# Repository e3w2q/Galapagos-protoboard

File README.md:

# Galapagos Protoboard

## Important point

All functions have not yet been verified on an actual device.

The microcontroller is one of the following: Pro Micro, Raspberry Pi Pico, or Xiao RP2040.

The key matrix is using duplex matrix.

You can use a rotary encoder or a joystick.

The joystick is one of the following:  ALPS RKJXV122400R, Nintendo Switch Joystick for Joy-Cons,  or Sparkfan joystick.

You may be able to use a trackball.

## Pin assign

### Key switch

|                         | Pro Micro | Raspberry Pi Pico | Xiao RP2040 |
| ----------------------- | --------- | ----------------- | ----------- |
| Upper left key switch   | F5 to D4  | GP9 to GP2        | GP6 to GP26 |
| Lower left key switch   | F5 to C6  | GP9 to GP3        | GP6 to GP27 |
| Upper middle key switch | D4 to F6  | GP2 to GP10       | GP26 to GP7 |
| Lower middle key switch | C6 to F6  | GP3 to GP10       | GP27 to GP7 |
| Upper right key switch  | D4 to F5  | GP2 to GP9        | GP26 to GP6 |
| Lower right key switch  | C6 to F5  | GP3 to GP9        | GP27 to GP6 |

### Rotary Encoder

|             | Pro Micro | Raspberry Pi Pico | Xiao RP2040 |
| ----------- | --------- | ----------------- | ----------- |
| A           | D1        | GP20              | No assign   |
| B           | D0        | GP21              | No assign   |
| Push switch | B6        | GP22              | No assign   |

### Joystick

|             | Pro Micro | Raspberry Pi Pico | Xiao RP2040 |
| ----------- | --------- | ----------------- | ----------- |
| Horizontal  | D1        | GP20              | No assign   |
| Vertical    | D0        | GP21              | No assign   |
| Push switch | B6        | GP22              | No assign   |

### Trackball

|             | Pro Micro | Raspberry Pi Pico | Xiao RP2040 |
| ----------- | --------- | ----------------- | ----------- |
| MISO        | B3        | GP16              | No assign   |
| MOSI        | B2        | GP19              | No assign   |
| SCLK        | B1        | GP18              | No assign   |
| NCS         | F7        | GP17              | No assign   |

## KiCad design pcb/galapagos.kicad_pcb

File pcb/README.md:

# Galapagos Protoboard

## Schematic
[Schematic PDF](../image/ukiha.pdf?raw=true)

## PCB Layout

## Acrylic Layout

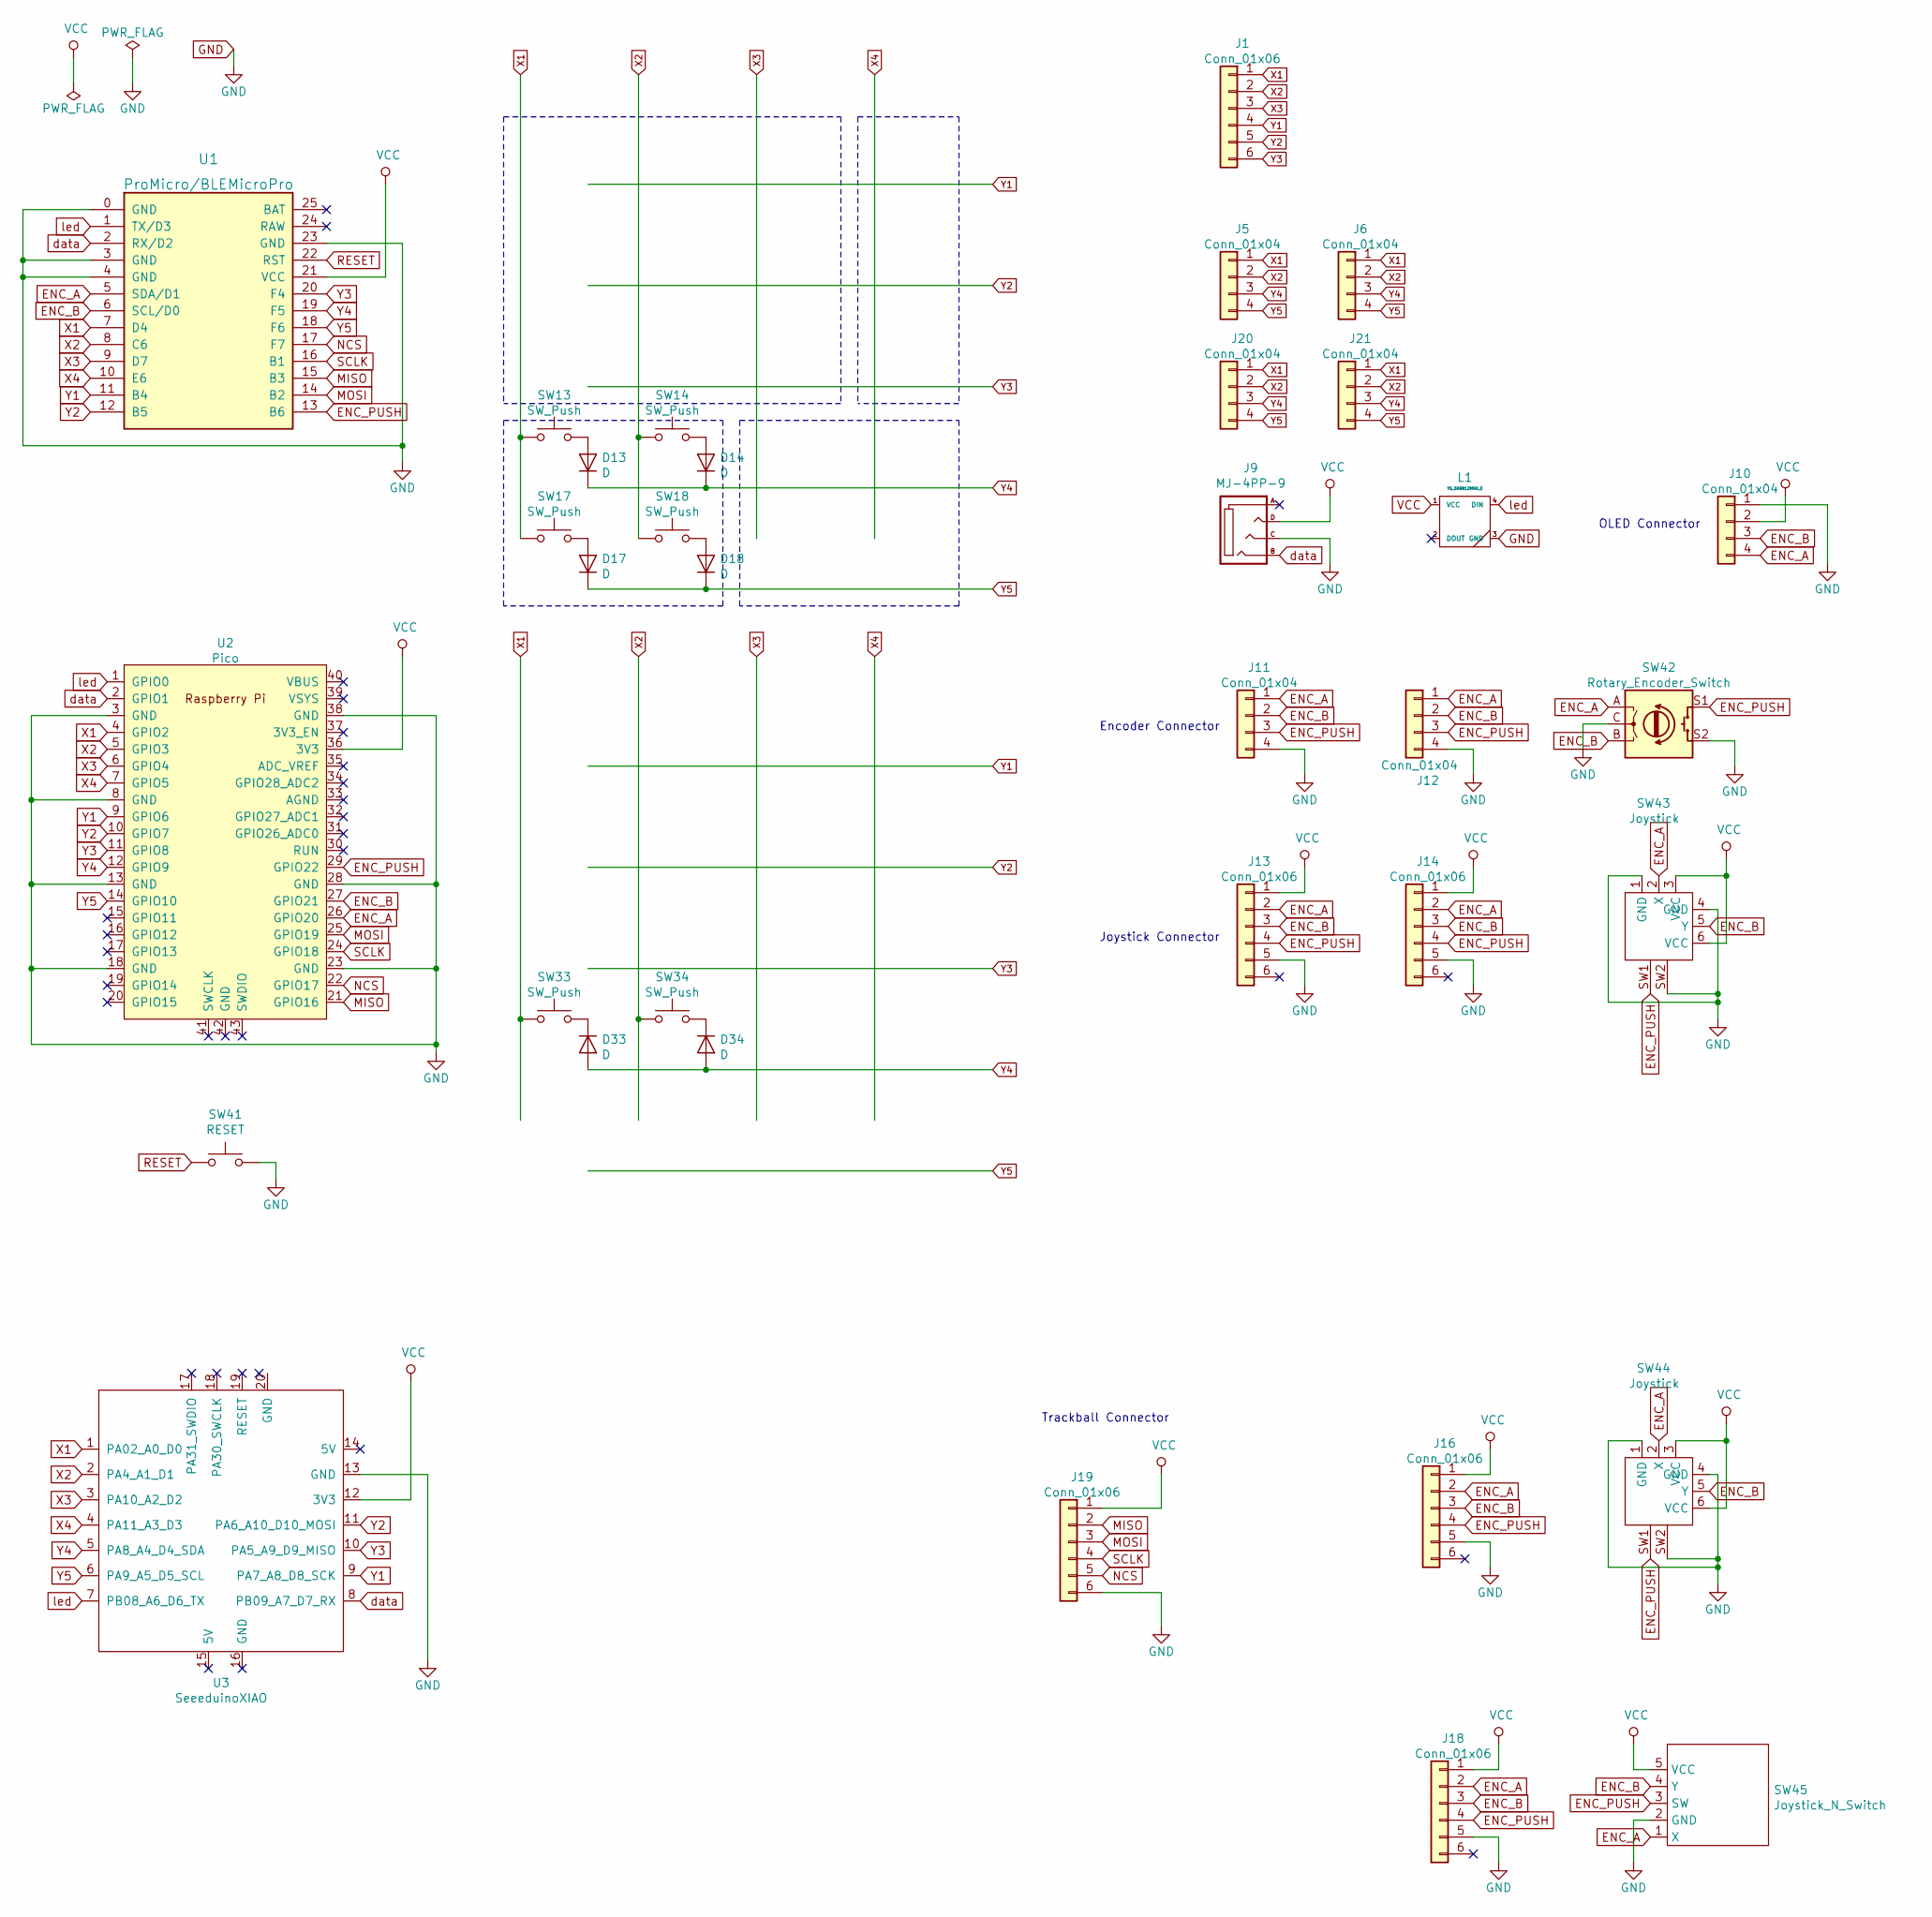
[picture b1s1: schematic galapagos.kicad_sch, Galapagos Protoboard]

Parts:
D13, D14, D17, D18, D33, D34: D; diode_TH_SMD_rev3
J1, J13, J14, J16, J18, J19: Conn_01x06; JST_SH_BM03B-SRSS-TB_1x06-1MP_P1.00mm_Vertical
J5, J6, J11, J12: Conn_01x04; JST_SH_BM03B-SRSS-TB_1x04-1MP_P1.00mm_Vertical
J9: MJ-4PP-9; MJ-4PP-9_reversible
J10: Conn_01x04; PinHeader_1x04_P2.54mm_Vertical
J20, J21: Conn_01x04; JST_ZH_1x04_P1.50mm_Vertical
L1: YS_SK6812MINI_E; YS-SK6812MINI-E
SW13, SW14, SW17, SW18, SW33, SW34: SW_Push; CherryMX_MidHeight_Choc_Hotswap_rev8_test
SW41: RESET; ResetSW
SW42: Rotary_Encoder_Switch; RotaryEncoder_Alps_EC11E-Switch_Vertical_H20mm_rev2
SW43: Joystick; Joystick_AE-RKJXV122400R
SW44: Joystick; Joystick_Sparkfan
SW45: Joystick_N_Switch
U1: ProMicro/BLEMicroPro; ArduinoProMicro_ConThrough
U2: Pico; RPi_Pico_SMD_TH_rev3
U3: SeeeduinoXIAO; Seeeduino XIAO RP2040

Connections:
ENC_A: J10.4, J11.1, J12.1, J13.2, J14.2, J16.2, J18.2, SW42.A, SW43.2 (X), SW44.2 (X), SW45.1 (X), U1.5 (SDA/D1), U2.26 (GPIO20)
ENC_B: J10.3, J11.2, J12.2, J13.3, J14.3, J16.3, J18.3, SW42.B, SW43.5 (Y), SW44.5 (Y), SW45.4 (Y), U1.6 (SCL/D0), U2.27 (GPIO21)
ENC_PUSH: J11.3, J12.3, J13.4, J14.4, J16.4, J18.4, SW42.S1, SW43.SW1, SW44.SW1, SW45.3 (SW), U1.13 (B6), U2.29 (GPIO22)
GND: J9.C, J10.1, J11.4, J12.4, J13.5, J14.5, J16.5, J18.5, J19.6, L1.3 (GND), SW41.2, SW42.C, SW42.S2, SW43.1 (GND), SW43.4 (GND), SW43.SW2, SW44.1 (GND), SW44.4 (GND), SW44.SW2, SW45.2 (GND), U1.0 (GND), U1.3 (GND), U1.4 (GND), U1.23 (GND), U2.3 (GND), U2.8 (GND), U2.13 (GND), U2.18 (GND), U2.23 (GND), U2.28 (GND), U2.38 (GND), U3.13 (GND)
MISO: J19.2, U1.15 (B3), U2.21 (GPIO16)
MOSI: J19.3, U1.14 (B2), U2.25 (GPIO19)
NCS: J19.5, U1.17 (F7), U2.22 (GPIO17)
unnamed: D13.2 (A), SW13.2
unnamed: D14.2 (A), SW14.2
unnamed: D17.2 (A), SW17.2
unnamed: D18.2 (A), SW18.2
unnamed: D33.1 (K), SW33.2
unnamed: D34.1 (K), SW34.2
RESET: SW41.1, U1.22 (RST)
SCLK: J19.4, U1.16 (B1), U2.24 (GPIO18)
VCC: J9.D, J10.2, J13.1, J14.1, J16.1, J18.1, J19.1, L1.1 (VCC), SW43.3 (VCC), SW43.6 (VCC), SW44.3 (VCC), SW44.6 (VCC), SW45.5 (VCC), U1.21 (VCC), U2.36 (3V3), U3.12 (3V3)
X1: J1.1, J5.1, J6.1, J20.1, J21.1, SW13.1, SW17.1, SW33.1, U1.7 (D4), U2.4 (GPIO2), U3.1 (PA02_A0_D0)
X2: J1.2, J5.2, J6.2, J20.2, J21.2, SW14.1, SW18.1, SW34.1, U1.8 (C6), U2.5 (GPIO3), U3.2 (PA4_A1_D1)
X3: J1.3, U1.9 (D7), U2.6 (GPIO4), U3.3 (PA10_A2_D2)
X4: U1.10 (E6), U2.7 (GPIO5), U3.4 (PA11_A3_D3)
Y1: J1.4, U1.11 (B4), U2.9 (GPIO6), U3.9 (PA7_A8_D8_SCK)
Y2: J1.5, U1.12 (B5), U2.10 (GPIO7), U3.11 (PA6_A10_D10_MOSI)
Y3: J1.6, U1.20 (F4), U2.11 (GPIO8), U3.10 (PA5_A9_D9_MISO)
Y4: D13.1 (K), D14.1 (K), D33.2 (A), D34.2 (A), J5.3, J6.3, J20.3, J21.3, U1.19 (F5), U2.12 (GPIO9), U3.5 (PA8_A4_D4_SDA)
Y5: D17.1 (K), D18.1 (K), J5.4, J6.4, J20.4, J21.4, U1.18 (F6), U2.14 (GPIO10), U3.6 (PA9_A5_D5_SCL)
data: J9.B, U1.2 (RX/D2), U2.2 (GPIO1), U3.8 (PB09_A7_D7_RX)
led: L1.4 (DIN), U1.1 (TX/D3), U2.1 (GPIO0), U3.7 (PB08_A6_D6_TX)

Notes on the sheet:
Trackball Connector
Encoder Connector
Joystick Connector
OLED Connector

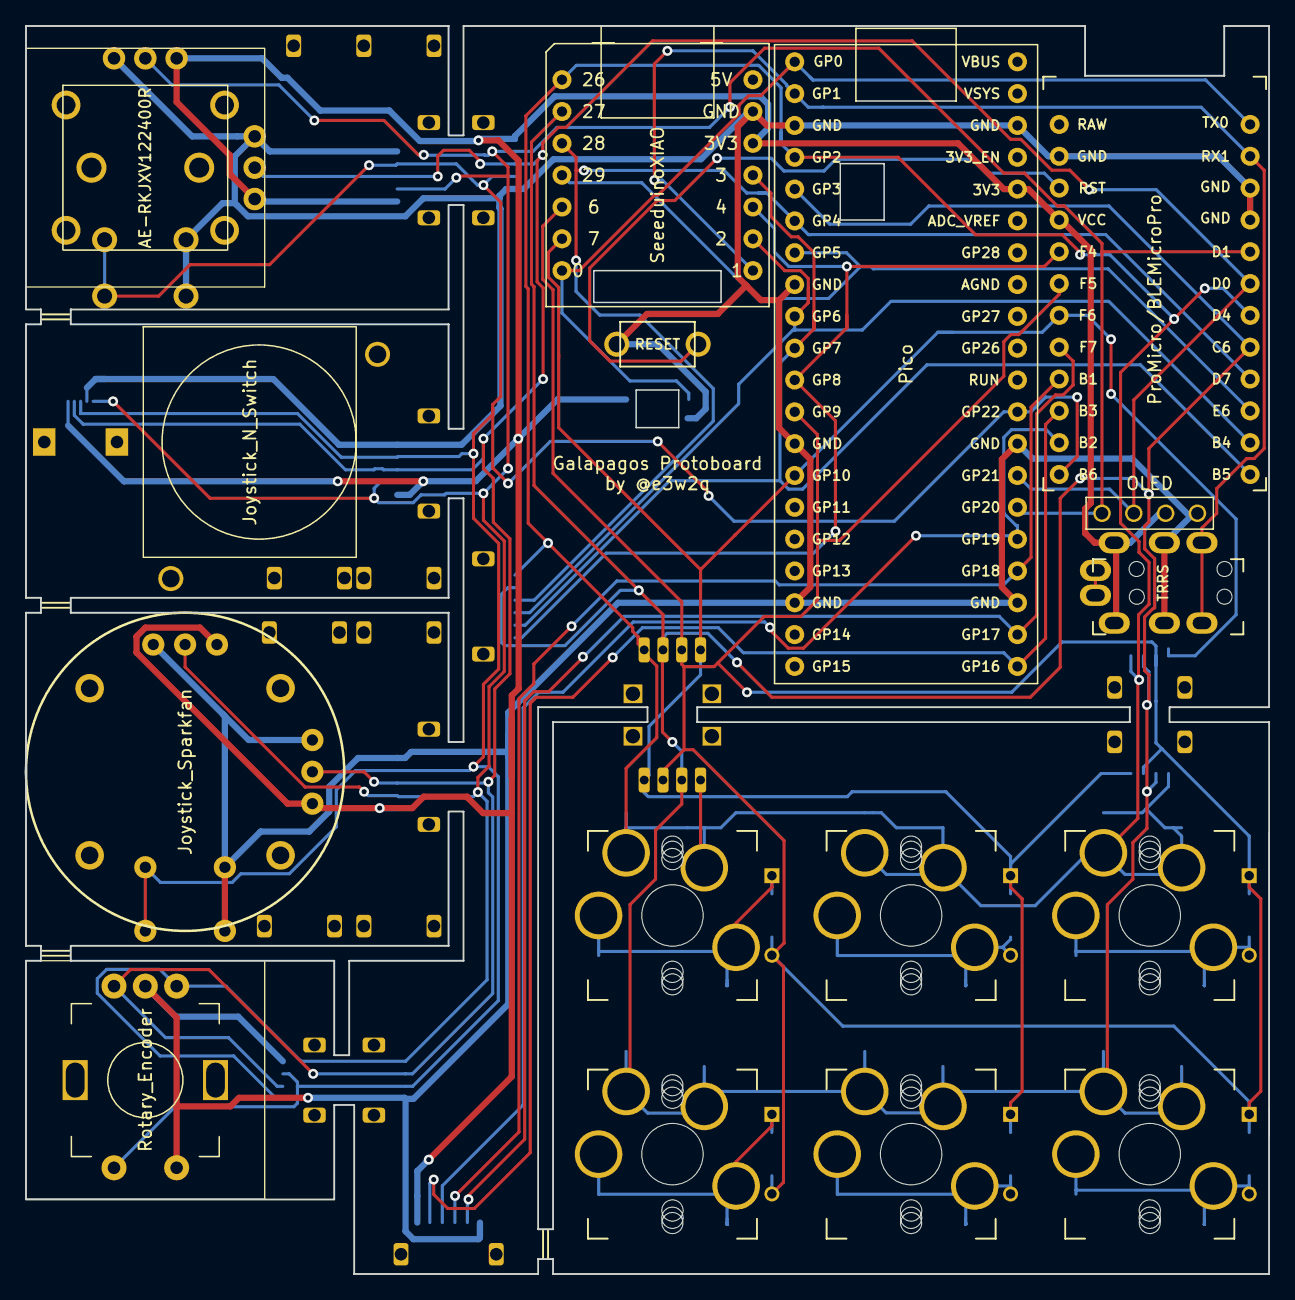
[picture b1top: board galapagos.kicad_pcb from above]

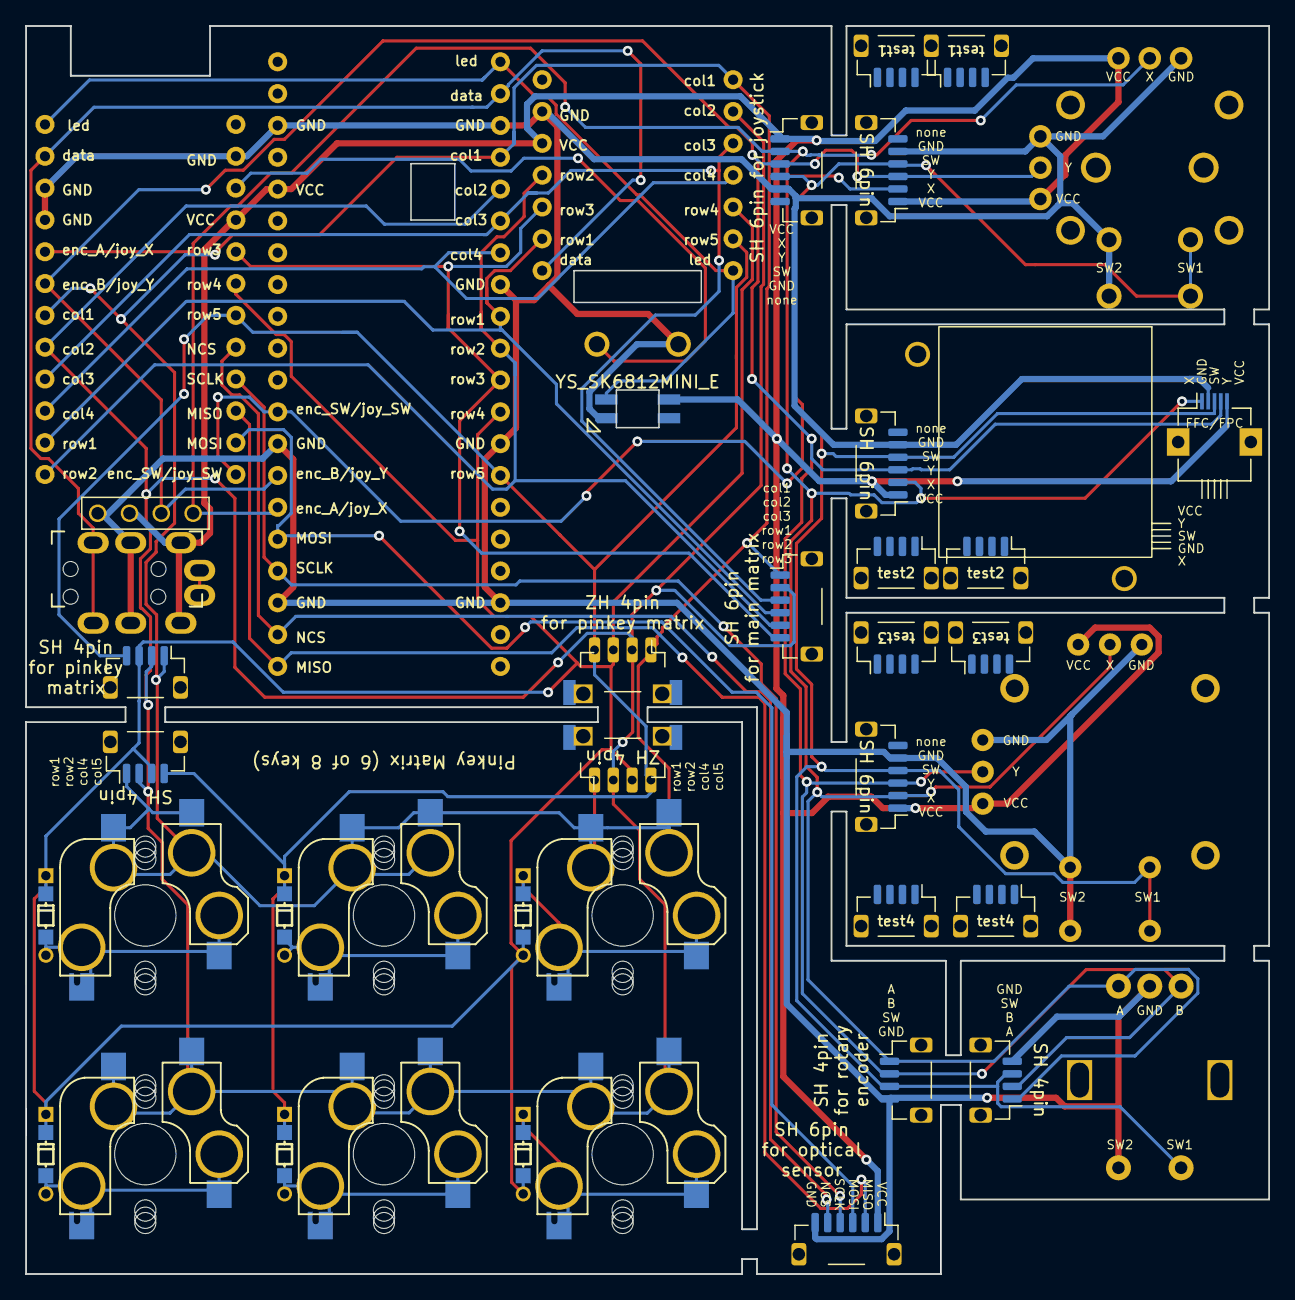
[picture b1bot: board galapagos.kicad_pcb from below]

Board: 2 copper layers, 99.2 x 99.6 mm, 35 parts (12 on the bottom side), 27 nets.
